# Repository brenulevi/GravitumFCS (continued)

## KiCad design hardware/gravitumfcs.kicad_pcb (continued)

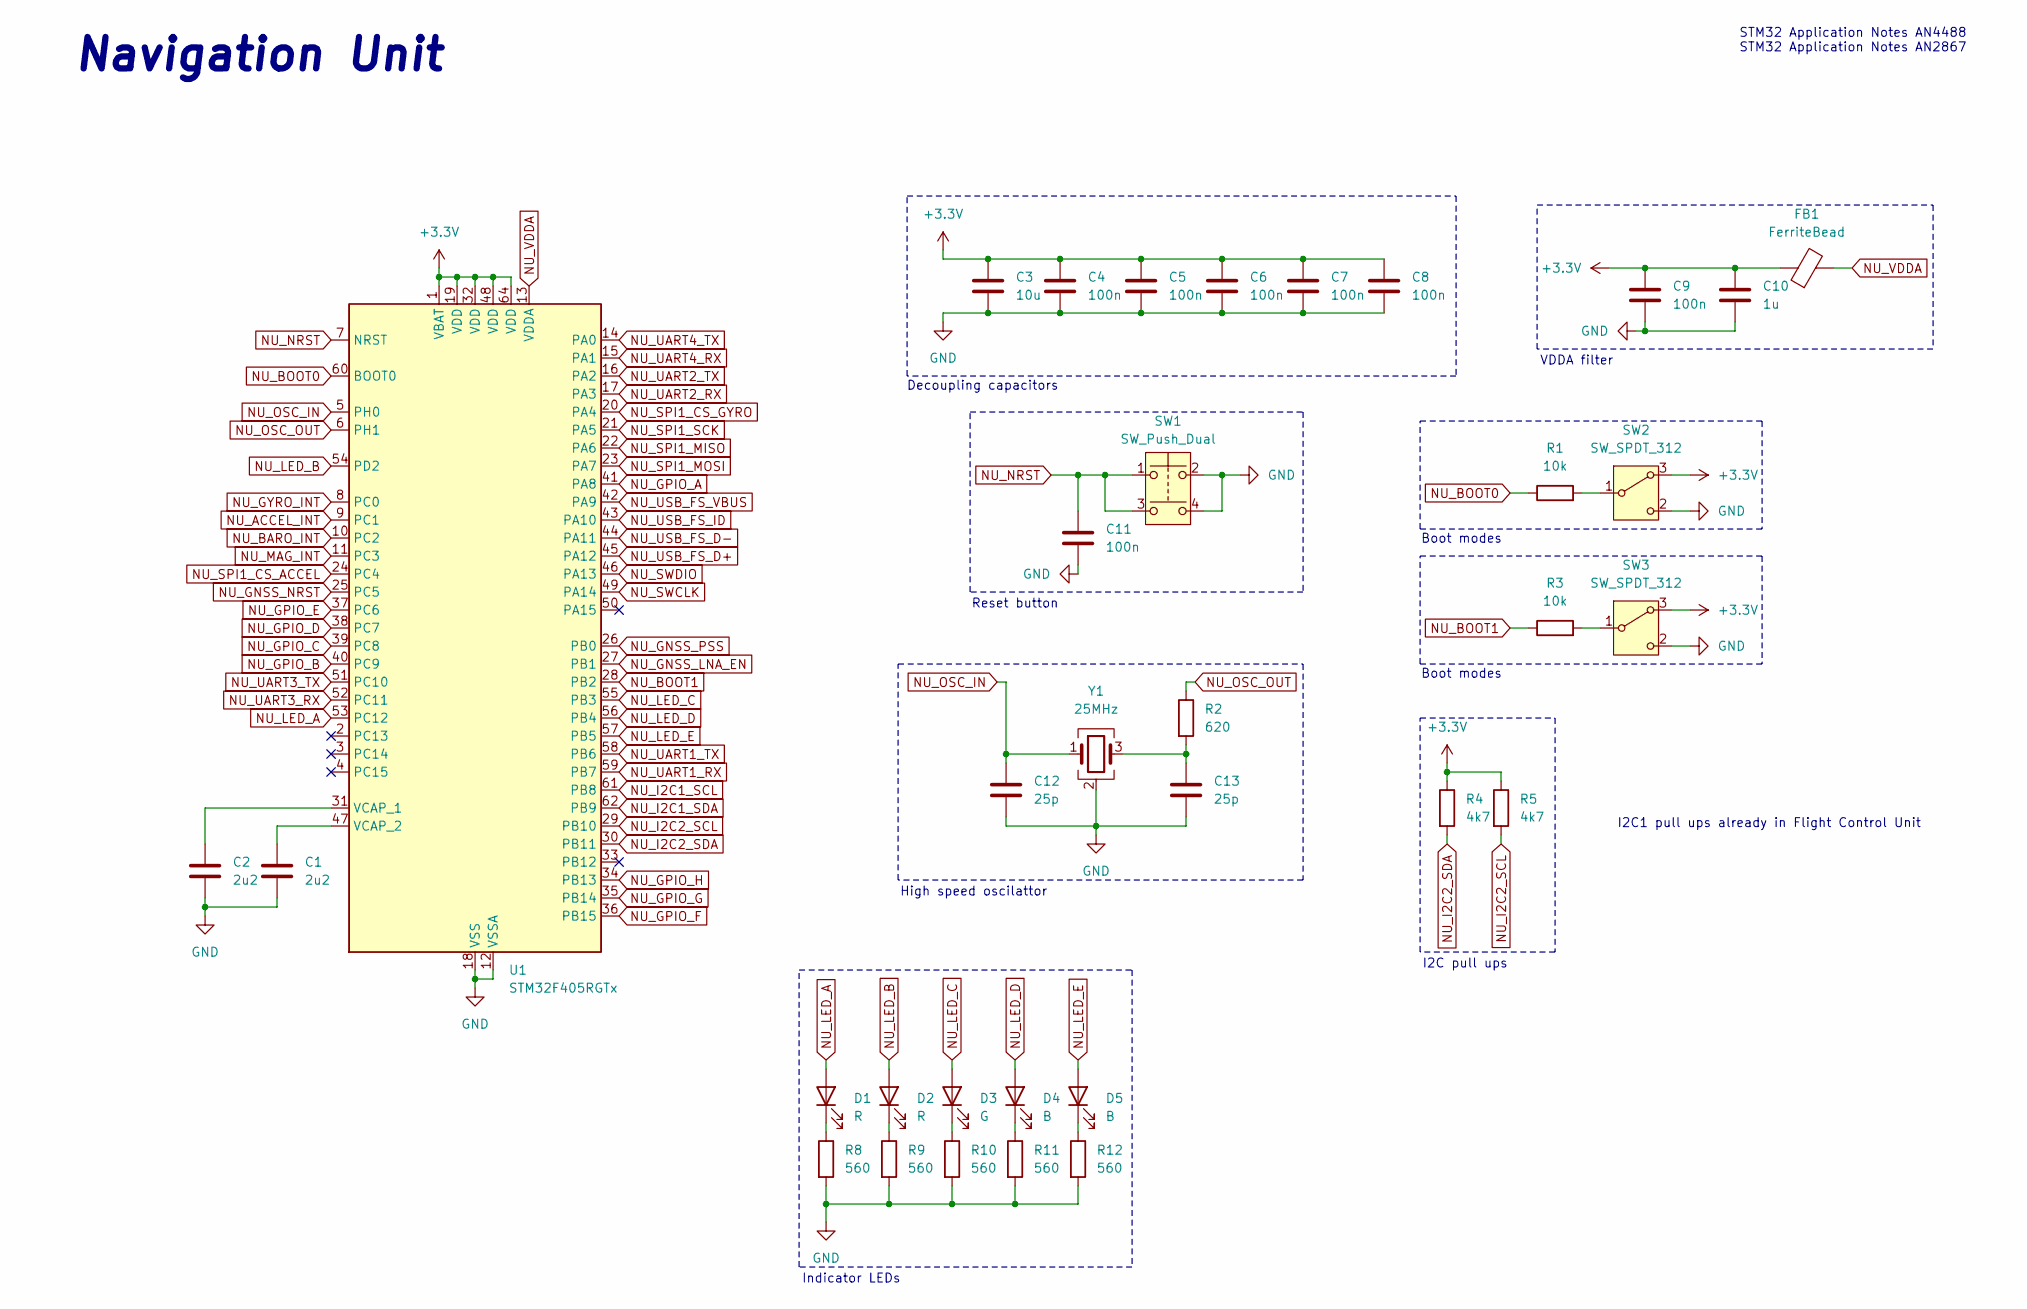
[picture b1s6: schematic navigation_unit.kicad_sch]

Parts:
C1, C2: 2u2; C_0805_2012Metric
C3: 10u; C_0603_1608Metric
C4, C5, C6, C7, C8, C9, C11: 100n; C_0402_1005Metric
C10: 1u; C_0603_1608Metric
C12, C13: 25p; C_0603_1608Metric
D1, D2: R; LED_0603_1608Metric
D3: G; LED_0603_1608Metric
D4, D5: B; LED_0603_1608Metric
FB1: FerriteBead; L_0603_1608Metric
R1, R3: 10k; R_0603_1608Metric
R2: 620; R_0603_1608Metric
R4, R5: 4k7; R_0603_1608Metric
R8, R9, R10, R11, R12: 560; R_0603_1608Metric
SW1: SW_Push_Dual; SW_TL3365AF180QG; Manufacturer Part Number TL3365AF180QG
SW2, SW3: SW_SPDT_312; SW_SPDT_PCM12; Manufacturer Part Number PCM12SMTR
U1: STM32F405RGTx; LQFP-64_10x10mm_P0.5mm; Manufacturer Part Number STM32F405RGT6
Y1: 25MHz; XTAL_ABM8G-25.000MHZ-18-D2Y-T; Manufacturer Part Number ABM8G-25.000MHZ-18-D2Y-T

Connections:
+3.3V: C3.1, C4.1, C5.1, C6.1, C7.1, C8.1, C9.1, C10.1, FB1.1, R4.1, R5.1, SW2.3 (A), SW3.3 (A), U1.1 (VBAT), U1.19 (VDD), U1.32 (VDD), U1.48 (VDD), U1.64 (VDD); also elsewhere on the board
GND: C1.2, C2.2, C3.2, C4.2, C5.2, C6.2, C7.2, C8.2, C9.2, C10.2, C11.2, C12.2, C13.2, R8.2, R9.2, R10.2, R11.2, R12.2, SW1.2, SW1.4, SW2.2 (C), SW3.2 (C), U1.12 (VSSA), U1.18 (VSS), U1.63 (VSS), Y1.2 (G), Y1.4 (G); also elsewhere on the board
NU_ACCEL_INT: U1.9 (PC1); also elsewhere on the board
NU_BARO_INT: U1.10 (PC2); also elsewhere on the board
NU_BOOT0: R1.1, U1.60 (BOOT0)
NU_BOOT1: R3.1, U1.28 (PB2)
NU_GNSS_LNA_EN: U1.27 (PB1); also elsewhere on the board
NU_GNSS_NRST: U1.25 (PC5); also elsewhere on the board
NU_GNSS_PSS: U1.26 (PB0); also elsewhere on the board
NU_GPIO_A: U1.41 (PA8); also elsewhere on the board
NU_GPIO_B: U1.40 (PC9); also elsewhere on the board
NU_GPIO_C: U1.39 (PC8); also elsewhere on the board
NU_GPIO_D: U1.38 (PC7); also elsewhere on the board
NU_GPIO_E: U1.37 (PC6); also elsewhere on the board
NU_GPIO_F: U1.36 (PB15); also elsewhere on the board
NU_GPIO_G: U1.35 (PB14); also elsewhere on the board
NU_GPIO_H: U1.34 (PB13); also elsewhere on the board
NU_GYRO_INT: U1.8 (PC0); also elsewhere on the board
NU_I2C1_SCL: U1.61 (PB8); also elsewhere on the board
NU_I2C1_SDA: U1.62 (PB9); also elsewhere on the board
NU_I2C2_SCL: R5.2, U1.29 (PB10); also elsewhere on the board
NU_I2C2_SDA: R4.2, U1.30 (PB11); also elsewhere on the board
NU_LED_A: D1.2 (A), U1.53 (PC12)
NU_LED_B: D2.2 (A), U1.54 (PD2)
NU_LED_C: D3.2 (A), U1.55 (PB3)
NU_LED_D: D4.2 (A), U1.56 (PB4)
NU_LED_E: D5.2 (A), U1.57 (PB5)
NU_MAG_INT: U1.11 (PC3); also elsewhere on the board
NU_NRST: C11.1, SW1.1, SW1.3, U1.7 (NRST); also elsewhere on the board
NU_OSC_IN: C12.1, U1.5 (PH0), Y1.1
NU_OSC_OUT: R2.1, U1.6 (PH1)
NU_SPI1_CS_ACCEL: U1.24 (PC4); also elsewhere on the board
NU_SPI1_CS_GYRO: U1.20 (PA4); also elsewhere on the board
NU_SPI1_MISO: U1.22 (PA6); also elsewhere on the board
NU_SPI1_MOSI: U1.23 (PA7); also elsewhere on the board
NU_SPI1_SCK: U1.21 (PA5); also elsewhere on the board
NU_SWCLK: U1.49 (PA14); also elsewhere on the board
NU_SWDIO: U1.46 (PA13); also elsewhere on the board
NU_UART1_RX: U1.59 (PB7); also elsewhere on the board
NU_UART1_TX: U1.58 (PB6); also elsewhere on the board
NU_UART2_RX: U1.17 (PA3); also elsewhere on the board
NU_UART2_TX: U1.16 (PA2); also elsewhere on the board
NU_UART3_RX: U1.52 (PC11); also elsewhere on the board
NU_UART3_TX: U1.51 (PC10); also elsewhere on the board
NU_UART4_RX: U1.15 (PA1); also elsewhere on the board
NU_UART4_TX: U1.14 (PA0); also elsewhere on the board
NU_USB_FS_D+: U1.45 (PA12); also elsewhere on the board
NU_USB_FS_D-: U1.44 (PA11); also elsewhere on the board
NU_USB_FS_ID: U1.43 (PA10); also elsewhere on the board
NU_USB_FS_VBUS: U1.42 (PA9); also elsewhere on the board
NU_VDDA: FB1.2, U1.13 (VDDA)
unnamed: C13.1, R2.2, Y1.3
unnamed: D1.1 (K), R8.1
unnamed: D2.1 (K), R9.1
unnamed: D3.1 (K), R10.1
unnamed: D4.1 (K), R11.1
unnamed: D5.1 (K), R12.1
unnamed: R1.2, SW2.1 (B)
unnamed: R3.2, SW3.1 (B)
unnamed: C2.1, U1.31 (VCAP_1)
unnamed: C1.1, U1.47 (VCAP_2)

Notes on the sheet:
I2C pull ups
I2C1 pull ups already in Flight Control Unit
Boot modes
Indicator LEDs
Navigation Unit
Reset button
STM32 Application Notes AN4488 STM32 Application Notes AN2867
VDDA filter
Decoupling capacitors
High speed oscilattor

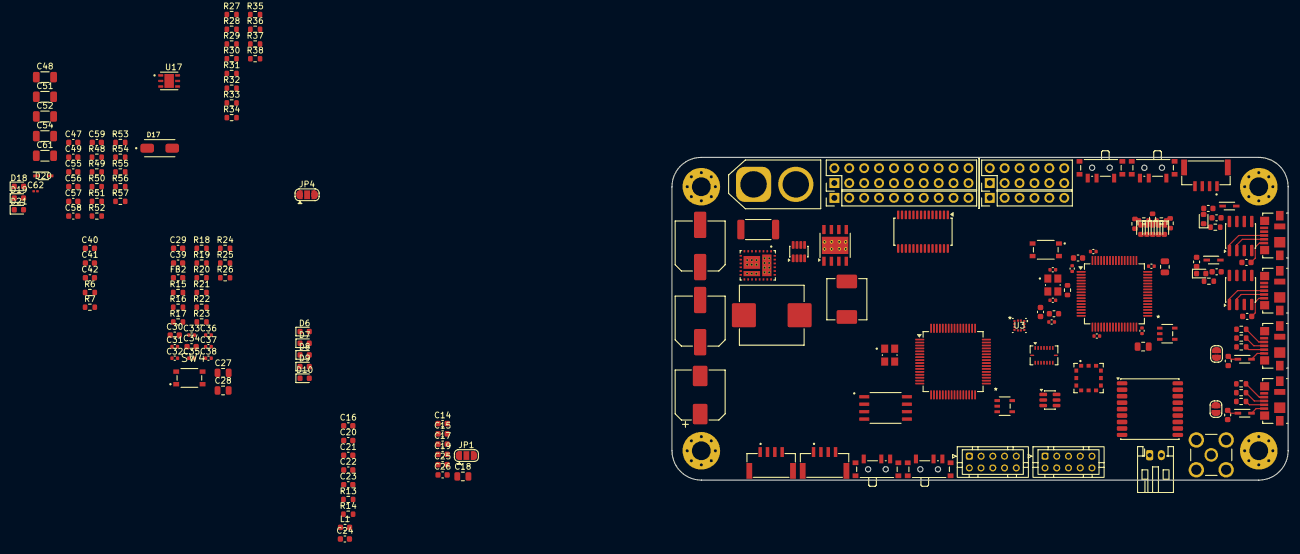
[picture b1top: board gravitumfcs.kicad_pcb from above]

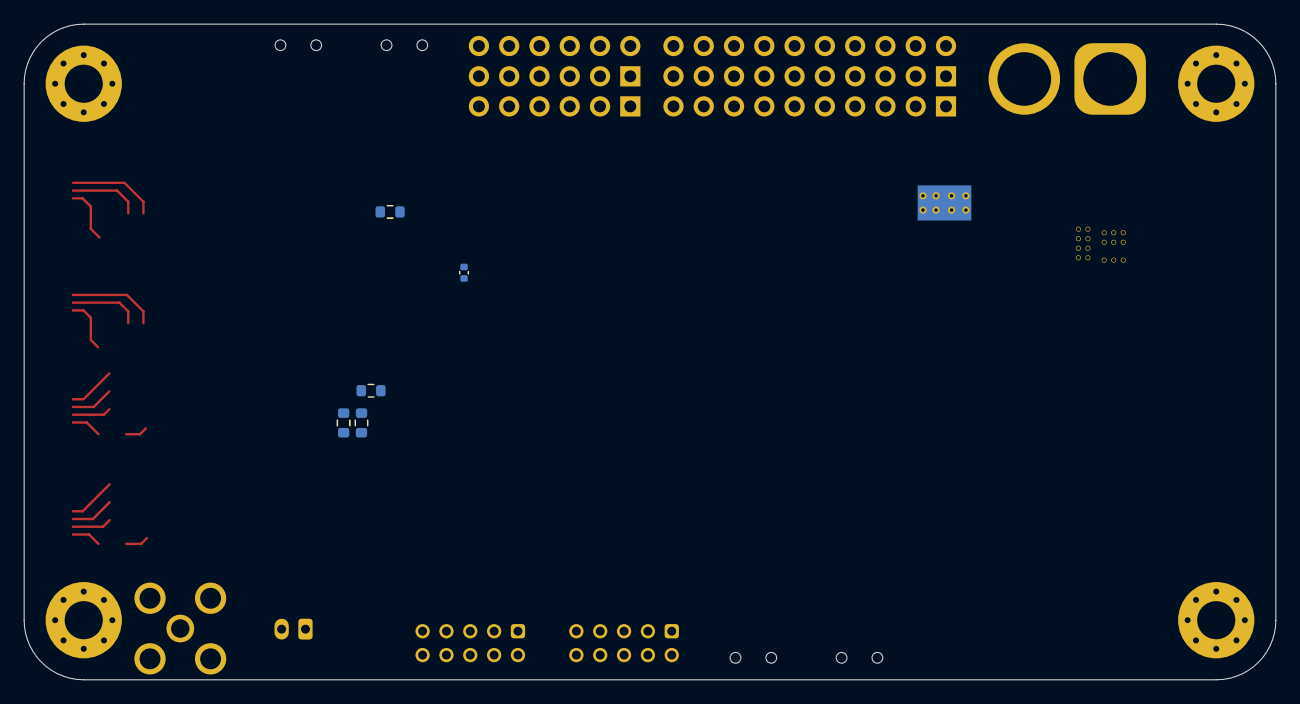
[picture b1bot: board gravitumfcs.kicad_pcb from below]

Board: 4 copper layers, 105.0 x 55.0 mm, 194 parts (5 on the bottom side), 179 nets.

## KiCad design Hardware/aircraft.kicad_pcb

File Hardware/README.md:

# FCU
- UART1: Comm with NU
- UART2: Logging Debug
- UART3: Extra UART (Radio Control)
- UART4: Extra UART (Camera)

- I2C1: Comm with NU
- I2C2: Peripherals (PWM Driver, EEPROM)

- TIM3: Actuators (CH1 Ailerons, CH2 Elevator, CH3 Rudder, CH4 Flaps)
- TIM1: Propulsions (CH2 ESC1, CH3 ESC2)

- SPI1: Peripherals (Flash)

- SWD: Coding/Debug

- SDIO: SD Card (1bit)

- GPIOA, GPIOC, GPIOE: Comm with NU (Output)
- GPIOB, GPIOD, GPIOF: Comm with NU (Input)

# NU
- UART1: Comm with FCU
- UART2: Logging Debug
- UART3: Peripheral (GNSS)
- UART4: Extra UART

- I2C1: Comm with FCU
- I2C2: Peripherals (Temperature, Baro, EEPROM, MAG)
- I2C3: Extra I2C (Pitot Sensor)

- SPI1: Peripherals (Flash) + 1 GPIO CS
- SPI2: Peripherals (IMU) + 1 GPIO CS

- SWD: Coding/Debug

- GPIO_GPS_PSS
- GPIO_GPS_LNA_EN
- GPIO_GPS_NRST

- GPIOA, GPIOC, GPIOE: Comm with NU (Input)
- GPIOB, GPIOD, GPIOF: Comm with NU (Output)

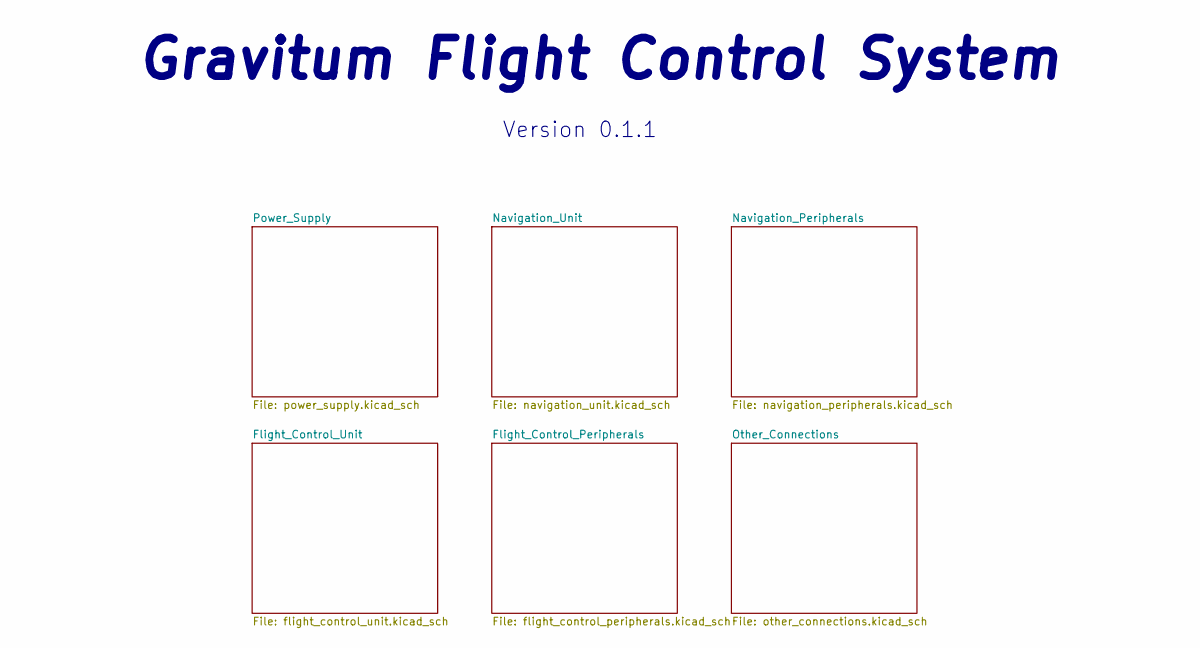
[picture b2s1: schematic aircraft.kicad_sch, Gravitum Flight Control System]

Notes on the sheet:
Gravitum Flight Control System
Version 0.1.1

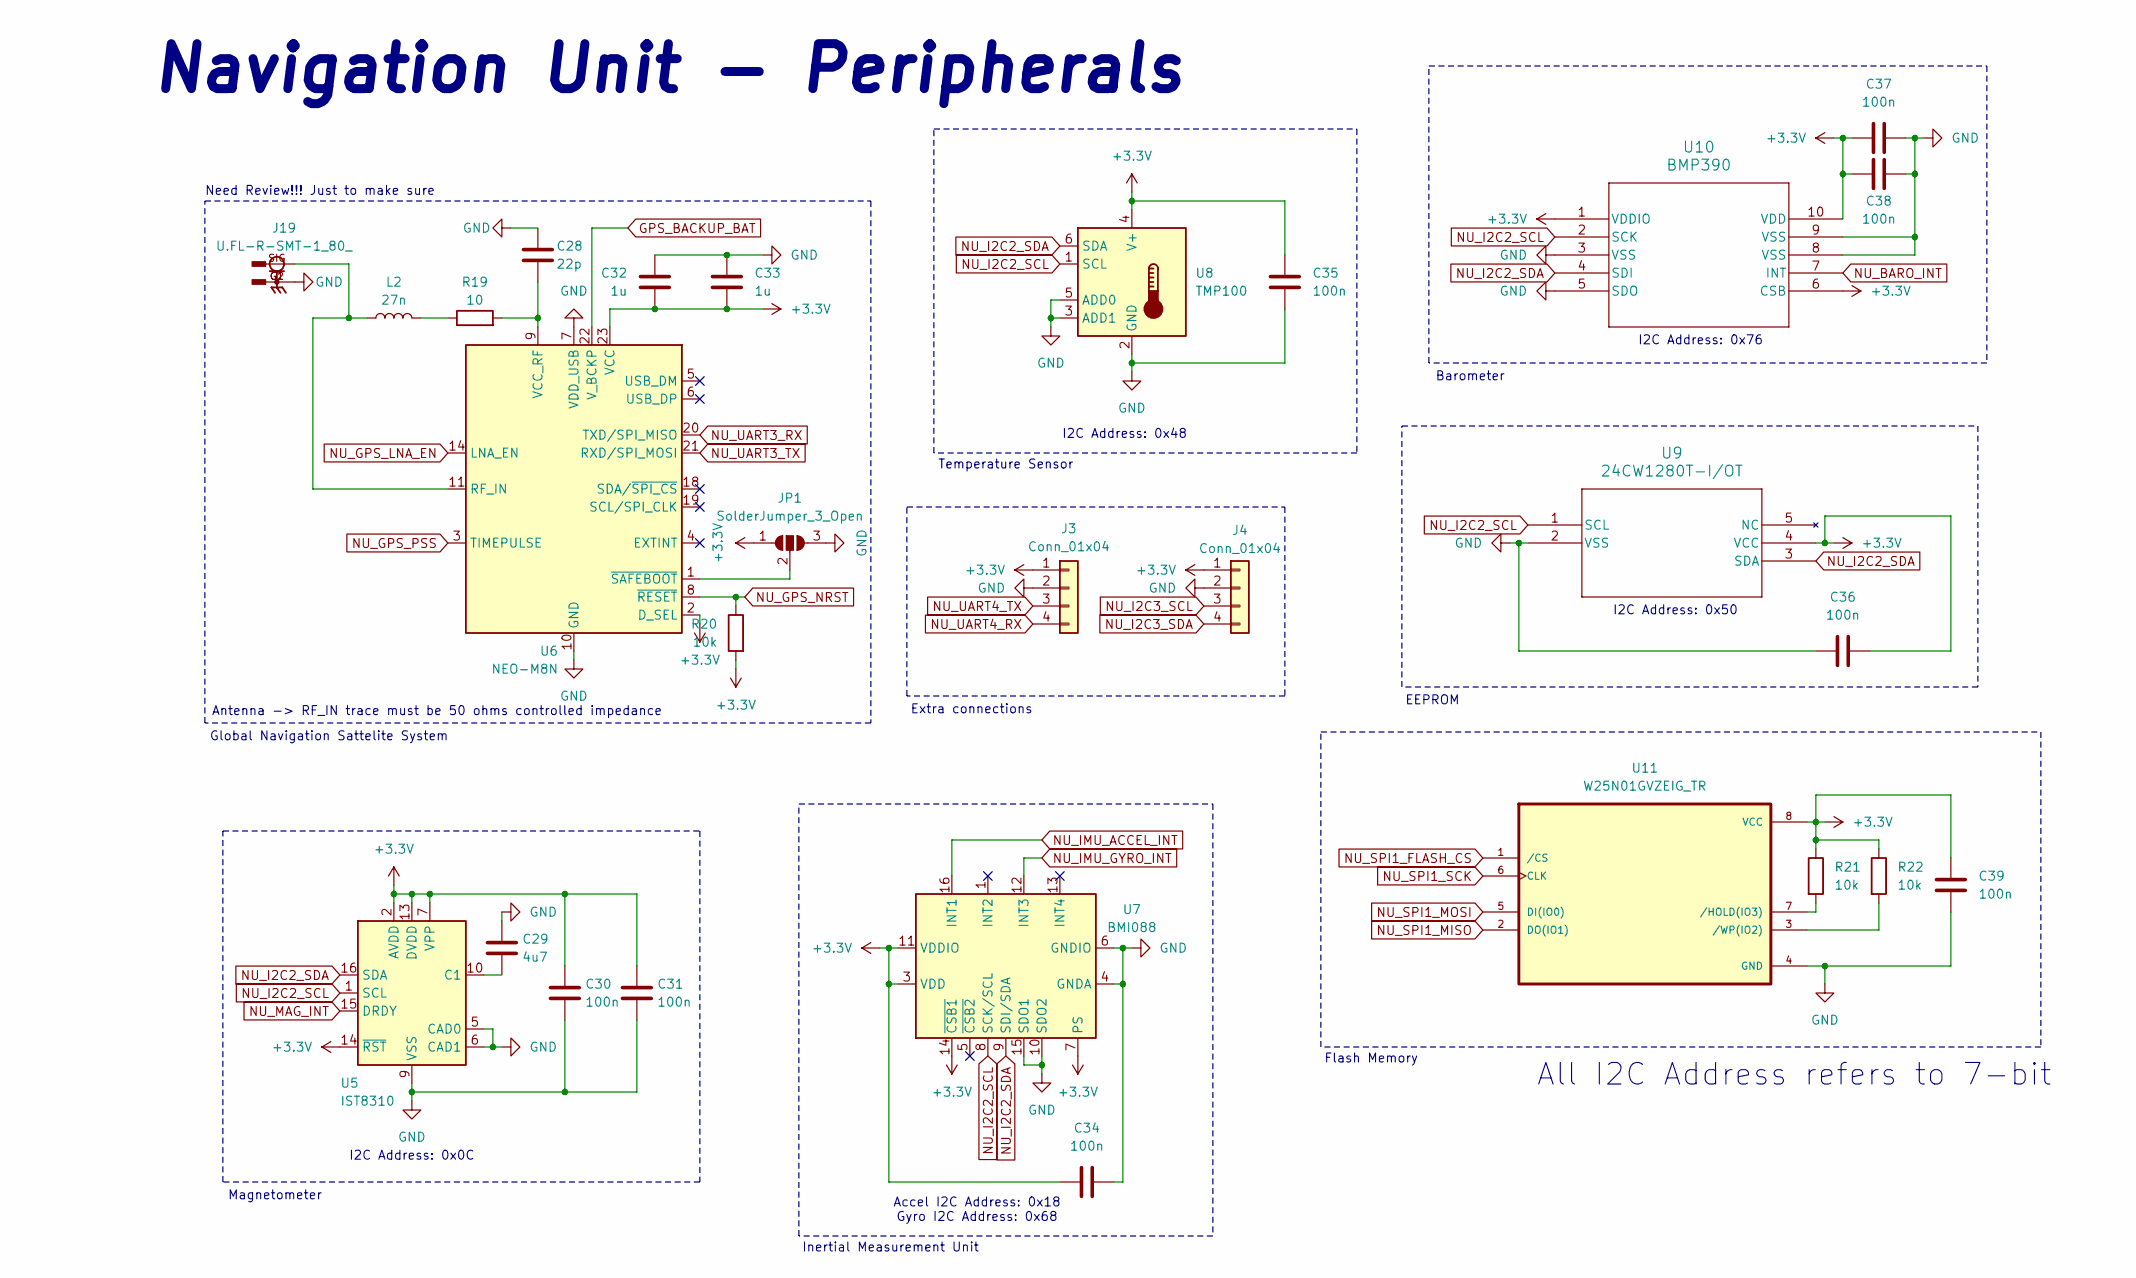
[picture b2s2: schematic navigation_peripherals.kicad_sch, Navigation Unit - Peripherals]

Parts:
C28: 22p; C_0402_1005Metric; MPN C0603C220J8GACTU
C29: 4u7; C_0402_1005Metric; MPN CL21B475KPFNNNE
C30, C31, C34, C35, C36, C37, C38, C39: 100n; C_0402_1005Metric; MPN C0603C104K8RACTU
C32, C33: 1u; C_0402_1005Metric; MPN CL10B105KP8NNNC
J3, J4: Conn_01x04; JST_PH_S4B-PH-K_1x04_P2.00mm_Horizontal; MPN S4B-PH-K-S
J19: U.FL-R-SMT-1_80_; HIROSE_U.FL-R-SMT-1_80_; PARTREV Jul.1.2022
JP1: SolderJumper_3_Open; SolderJumper-3_P1.3mm_Open_RoundedPad1.0x1.5mm_NumberLabels
L2: 27n; L_0402_1005Metric; MPN B82496C3270J000
R19: 10; R_0402_1005Metric; MPN RMCF0603FT10R0
R20, R21, R22: 10k; R_0402_1005Metric; MPN RC0603FR-0710KL
U5: IST8310; LGA-16_3x3mm_P0.5mm; MPN IST8310
U6: NEO-M8N; XCVR_NEO-M8N-0; MPN NEO-M8N-0
U7: BMI088; Bosch_LGA-16_4.5x3mm_P0.5mm_LayoutBorder7x1y_ClockwisePinNu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; MPN BMI088
U8: TMP100; SOT-23-6; MPN TMP100NA-3K
U9: 24CW1280T-I/OT; SOT-23-5_2P9X1P6_MCH; MPN 24CW1280T-I/OT
U10: BMP390; 10LGA_2X2X0p75_BOS; MPN BMP390
U11: W25N01GVZEIG_TR; SON127P800X600X80-9N; MPN W25N01GVZEIG-TR

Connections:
+3.3V: C30.1, C31.1, C32.2, C33.2, C34.1, C35.2, C36.1, C37.2, C38.2, C39.1, J3.1, J4.1, JP1.1 (A), R20.2, R21.1, R22.1, U5.2 (AVDD), U5.7 (VPP), U5.13 (DVDD), U5.14 (~RST), U6.2 (D_SEL), U6.23 (VCC), U7.3 (VDD), U7.7 (PS), U7.11 (VDDIO), U7.14 (~CSB1), U8.4 (V+), U9.4 (VCC), U10.1 (VDDIO), U10.6 (CSB), U10.10 (VDD), U11.8 (VCC); also elsewhere on the board
GND: C28.1, C29.1, C30.2, C31.2, C32.1, C33.1, C34.2, C35.1, C36.2, C37.1, C38.1, C39.2, J3.2, J4.2, J19.G1, J19.G2, JP1.3 (B), U5.5 (CAD0), U5.6 (CAD1), U5.9 (VSS), U5.11 (VSS), U6.7 (VDD_USB), U6.10 (GND), U6.12 (GND), U6.13 (GND), U6.24 (GND), U7.2 (GNDA), U7.4 (GNDA), U7.6 (GNDIO), U7.10 (SDO2), U7.15 (SDO1), U8.2 (GND), U8.3 (ADD1), U8.5 (ADD0), U9.2 (VSS), U10.3 (VSS), U10.5 (SDO), U10.8 (VSS), U10.9 (VSS), U11.4 (GND); also elsewhere on the board
GPS_BACKUP_BAT: U6.22 (V_BCKP); also elsewhere on the board
NU_BARO_INT: U10.7 (INT); also elsewhere on the board
NU_GPS_LNA_EN: U6.14 (LNA_EN); also elsewhere on the board
NU_GPS_NRST: R20.1, U6.8 (~RESET); also elsewhere on the board
NU_GPS_PSS: U6.3 (TIMEPULSE); also elsewhere on the board
NU_I2C2_SCL: U5.1 (SCL), U7.8 (SCK/SCL), U8.1 (SCL), U9.1 (SCL), U10.2 (SCK); also elsewhere on the board
NU_I2C2_SDA: U5.16 (SDA), U7.9 (SDI/SDA), U8.6 (SDA), U9.3 (SDA), U10.4 (SDI); also elsewhere on the board
NU_I2C3_SCL: J4.3; also elsewhere on the board
NU_I2C3_SDA: J4.4; also elsewhere on the board
NU_IMU_ACCEL_INT: U7.16 (INT1); also elsewhere on the board
NU_IMU_GYRO_INT: U7.12 (INT3); also elsewhere on the board
NU_MAG_INT: U5.15 (DRDY); also elsewhere on the board
NU_SPI1_FLASH_CS: U11.1 (/CS); also elsewhere on the board
NU_SPI1_MISO: U11.2 (DO(IO1)); also elsewhere on the board
NU_SPI1_MOSI: U11.5 (DI(IO0)); also elsewhere on the board
NU_SPI1_SCK: U11.6 (CLK); also elsewhere on the board
NU_UART3_RX: U6.20 (TXD/SPI_MISO); also elsewhere on the board
NU_UART3_TX: U6.21 (RXD/SPI_MOSI); also elsewhere on the board
NU_UART4_RX: J3.4; also elsewhere on the board
NU_UART4_TX: J3.3; also elsewhere on the board
unnamed: JP1.2 (C), U6.1 (~SAFEBOOT)
unnamed: L2.2, R19.1
unnamed: C29.2, U5.10 (C1)
unnamed: J19.SIG, L2.1, U6.11 (RF_IN)
unnamed: C28.2, R19.2, U6.9 (VCC_RF)
unnamed: R21.2, U11.7 (/HOLD(IO3))
unnamed: R22.2, U11.3 (/WP(IO2))

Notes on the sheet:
Magnetometer
Navigation Unit - Peripherals
I2C Address: 0x48
Flash Memory
I2C Address: 0x76
Barometer
Temperature Sensor
Accel I2C Address: 0x18 Gyro I2C Address: 0x68
EEPROM
Need Review!!! Just to make sure
Global Navigation Sattelite System
Inertial Measurement Unit
All I2C Address refers to 7-bit
Antenna -> RF_IN trace must be 50 ohms controlled impedance
I2C Address: 0x0C
I2C Address: 0x50
Extra connections

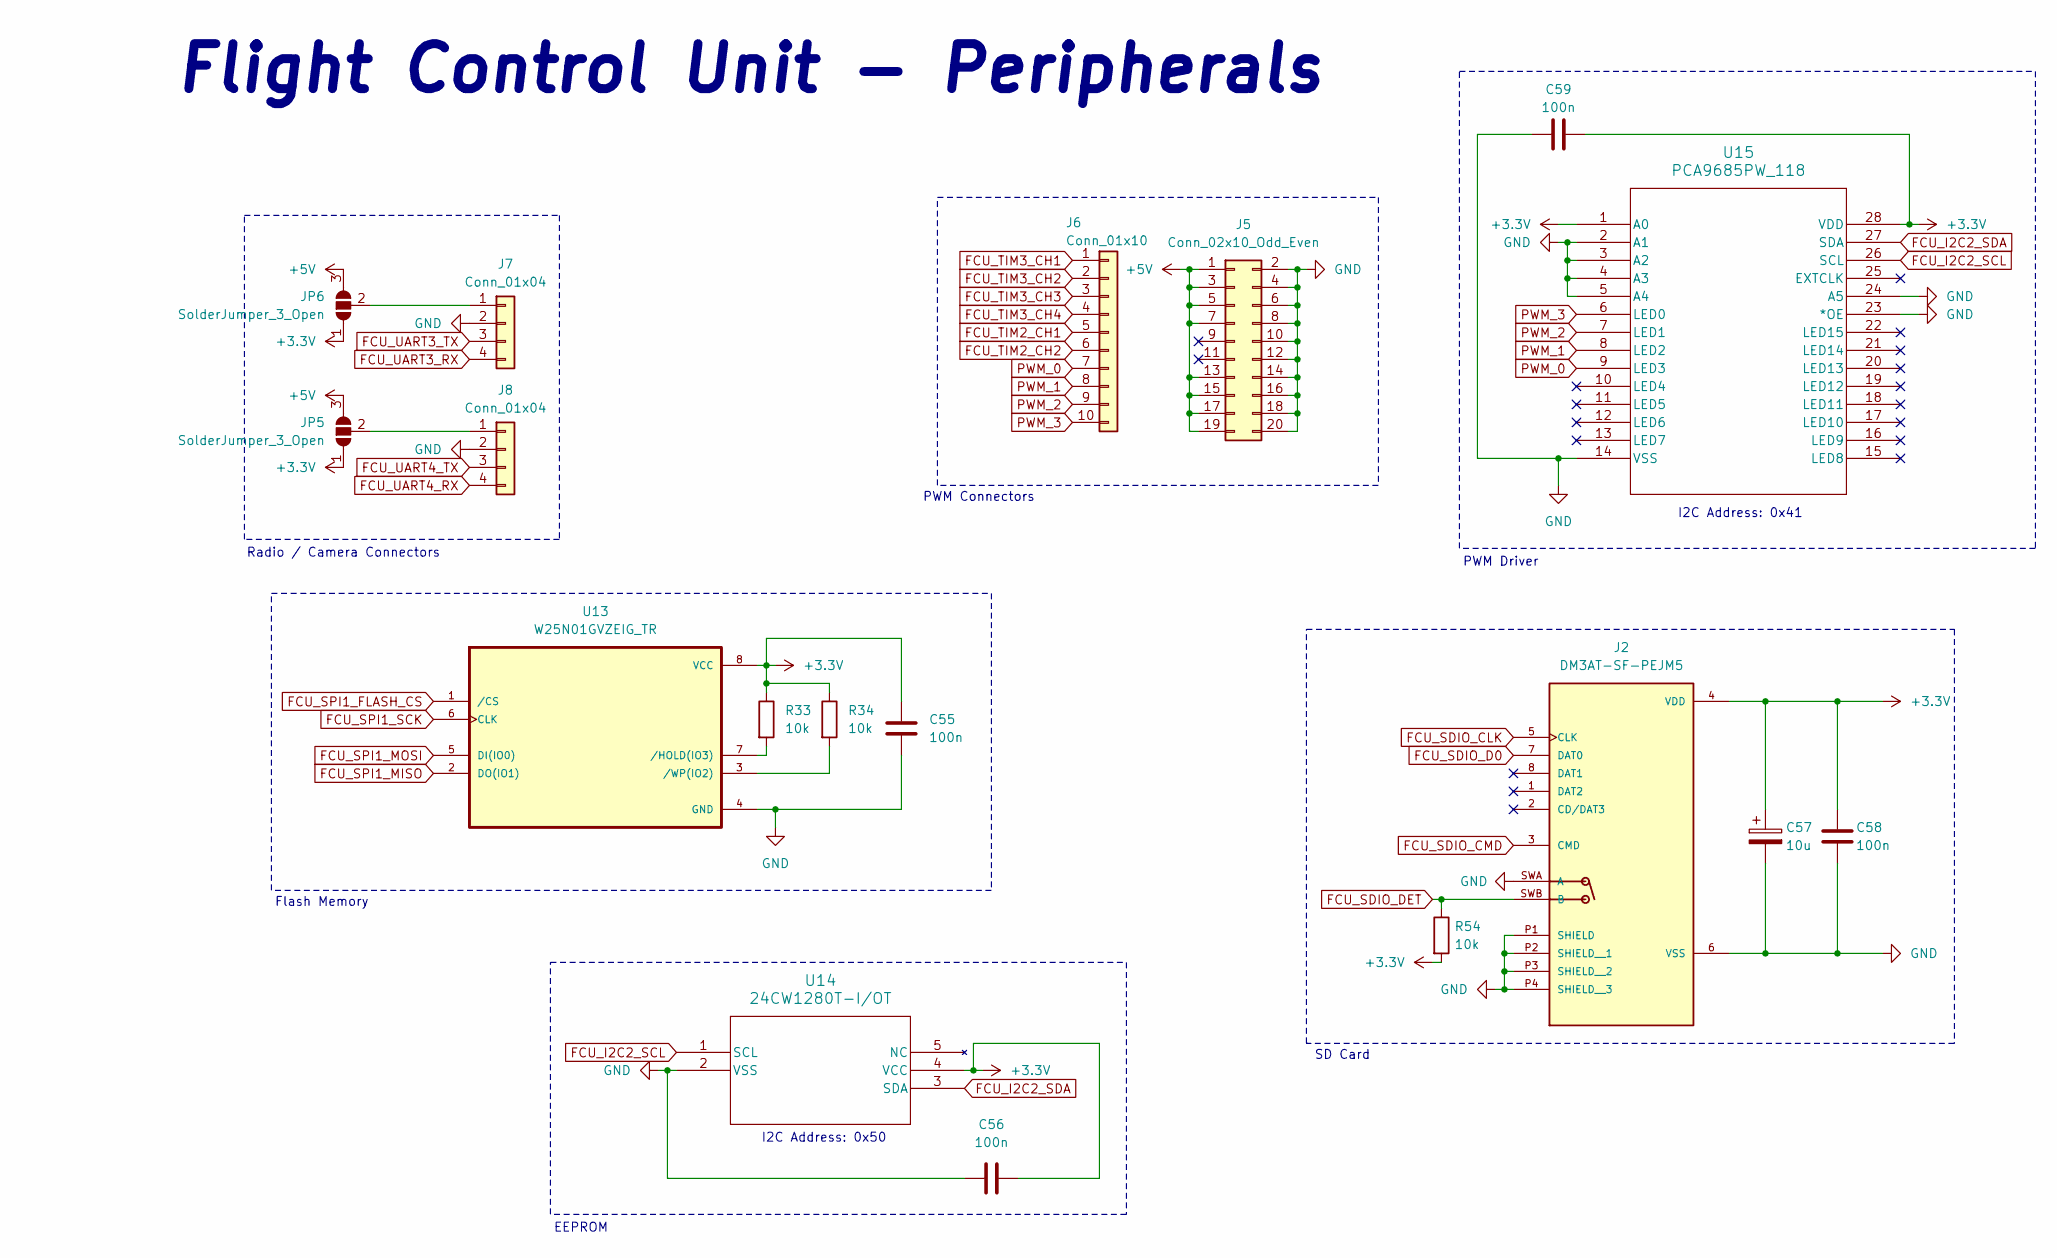
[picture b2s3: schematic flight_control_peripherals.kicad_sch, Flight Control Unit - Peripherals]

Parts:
C55, C56, C58, C59: 100n; C_0402_1005Metric; MPN C0603C104K8RACTU
C57: 10u; C_0603_1608Metric; MPN TAJA106K010TNJ
J2: DM3AT-SF-PEJM5; HRS_DM3AT-SF-PEJM5; PARTREV 20200913
J5: Conn_02x10_Odd_Even; PinHeader_2x10_P2.54mm_Vertical
J6: Conn_01x10; PinHeader_1x10_P2.54mm_Vertical
J7, J8: Conn_01x04; JST_PH_S4B-PH-K_1x04_P2.00mm_Horizontal; MPN S4B-PH-K-S
JP5, JP6: SolderJumper_3_Open; SolderJumper-3_P1.3mm_Open_RoundedPad1.0x1.5mm_NumberLabels
R33, R34, R54: 10k; R_0402_1005Metric; MPN RC0603FR-0710KL
U13: W25N01GVZEIG_TR; SON127P800X600X80-9N; MPN W25N01GVZEIG-TR
U14: 24CW1280T-I/OT; SOT-23-5_2P9X1P6_MCH; MPN 24CW1280T-I/OT
U15: PCA9685PW_118; TSSOP28_SOT361-1_NXP; MPN PCA9685PW,118

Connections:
+3.3V: C55.1, C56.1, C57.1, C58.1, C59.1, J2.4 (VDD), JP5.1 (A), JP6.1 (A), R33.1, R34.1, R54.2, U13.8 (VCC), U14.4 (VCC), U15.1 (A0), U15.28 (VDD); also elsewhere on the board
+5V: J5.1, J5.3, J5.5, J5.7, J5.13, J5.15, J5.17, J5.19, JP5.3 (B), JP6.3 (B); also elsewhere on the board
FCU_I2C2_SCL: U14.1 (SCL), U15.26 (SCL); also elsewhere on the board
FCU_I2C2_SDA: U14.3 (SDA), U15.27 (SDA); also elsewhere on the board
FCU_SDIO_CLK: J2.5 (CLK); also elsewhere on the board
FCU_SDIO_CMD: J2.3 (CMD); also elsewhere on the board
FCU_SDIO_D0: J2.7 (DAT0); also elsewhere on the board
FCU_SDIO_DET: J2.SWB (B), R54.1; also elsewhere on the board
FCU_SPI1_FLASH_CS: U13.1 (/CS); also elsewhere on the board
FCU_SPI1_MISO: U13.2 (DO(IO1)); also elsewhere on the board
FCU_SPI1_MOSI: U13.5 (DI(IO0)); also elsewhere on the board
FCU_SPI1_SCK: U13.6 (CLK); also elsewhere on the board
FCU_TIM2_CH1: J6.5; also elsewhere on the board
FCU_TIM2_CH2: J6.6; also elsewhere on the board
FCU_TIM3_CH1: J6.1; also elsewhere on the board
FCU_TIM3_CH2: J6.2; also elsewhere on the board
FCU_TIM3_CH3: J6.3; also elsewhere on the board
FCU_TIM3_CH4: J6.4; also elsewhere on the board
FCU_UART3_RX: J7.4; also elsewhere on the board
FCU_UART3_TX: J7.3; also elsewhere on the board
FCU_UART4_RX: J8.4; also elsewhere on the board
FCU_UART4_TX: J8.3; also elsewhere on the board
GND: C55.2, C56.2, C57.2, C58.2, C59.2, J2.6 (VSS), J2.P1 (SHIELD), J2.P2 (SHIELD__1), J2.P3 (SHIELD__2), J2.P4 (SHIELD__3), J2.SWA (A), J5.2, J5.4, J5.6, J5.8, J5.10, J5.12, J5.14, J5.16, J5.18, J5.20, J7.2, J8.2, U13.4 (GND), U14.2 (VSS), U15.2 (A1), U15.3 (A2), U15.4 (A3), U15.5 (A4), U15.14 (VSS), U15.23 (*OE), U15.24 (A5); also elsewhere on the board
unnamed: J7.1, JP6.2 (C)
unnamed: J8.1, JP5.2 (C)
unnamed: R33.2, U13.7 (/HOLD(IO3))
unnamed: R34.2, U13.3 (/WP(IO2))
PWM_0: J6.7, U15.9 (LED3)
PWM_1: J6.8, U15.8 (LED2)
PWM_2: J6.9, U15.7 (LED1)
PWM_3: J6.10, U15.6 (LED0)

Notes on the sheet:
I2C Address: 0x50
I2C Address: 0x41
Radio / Camera Connectors
SD Card
PWM Driver
PWM Connectors
Flash Memory
Flight Control Unit - Peripherals
EEPROM

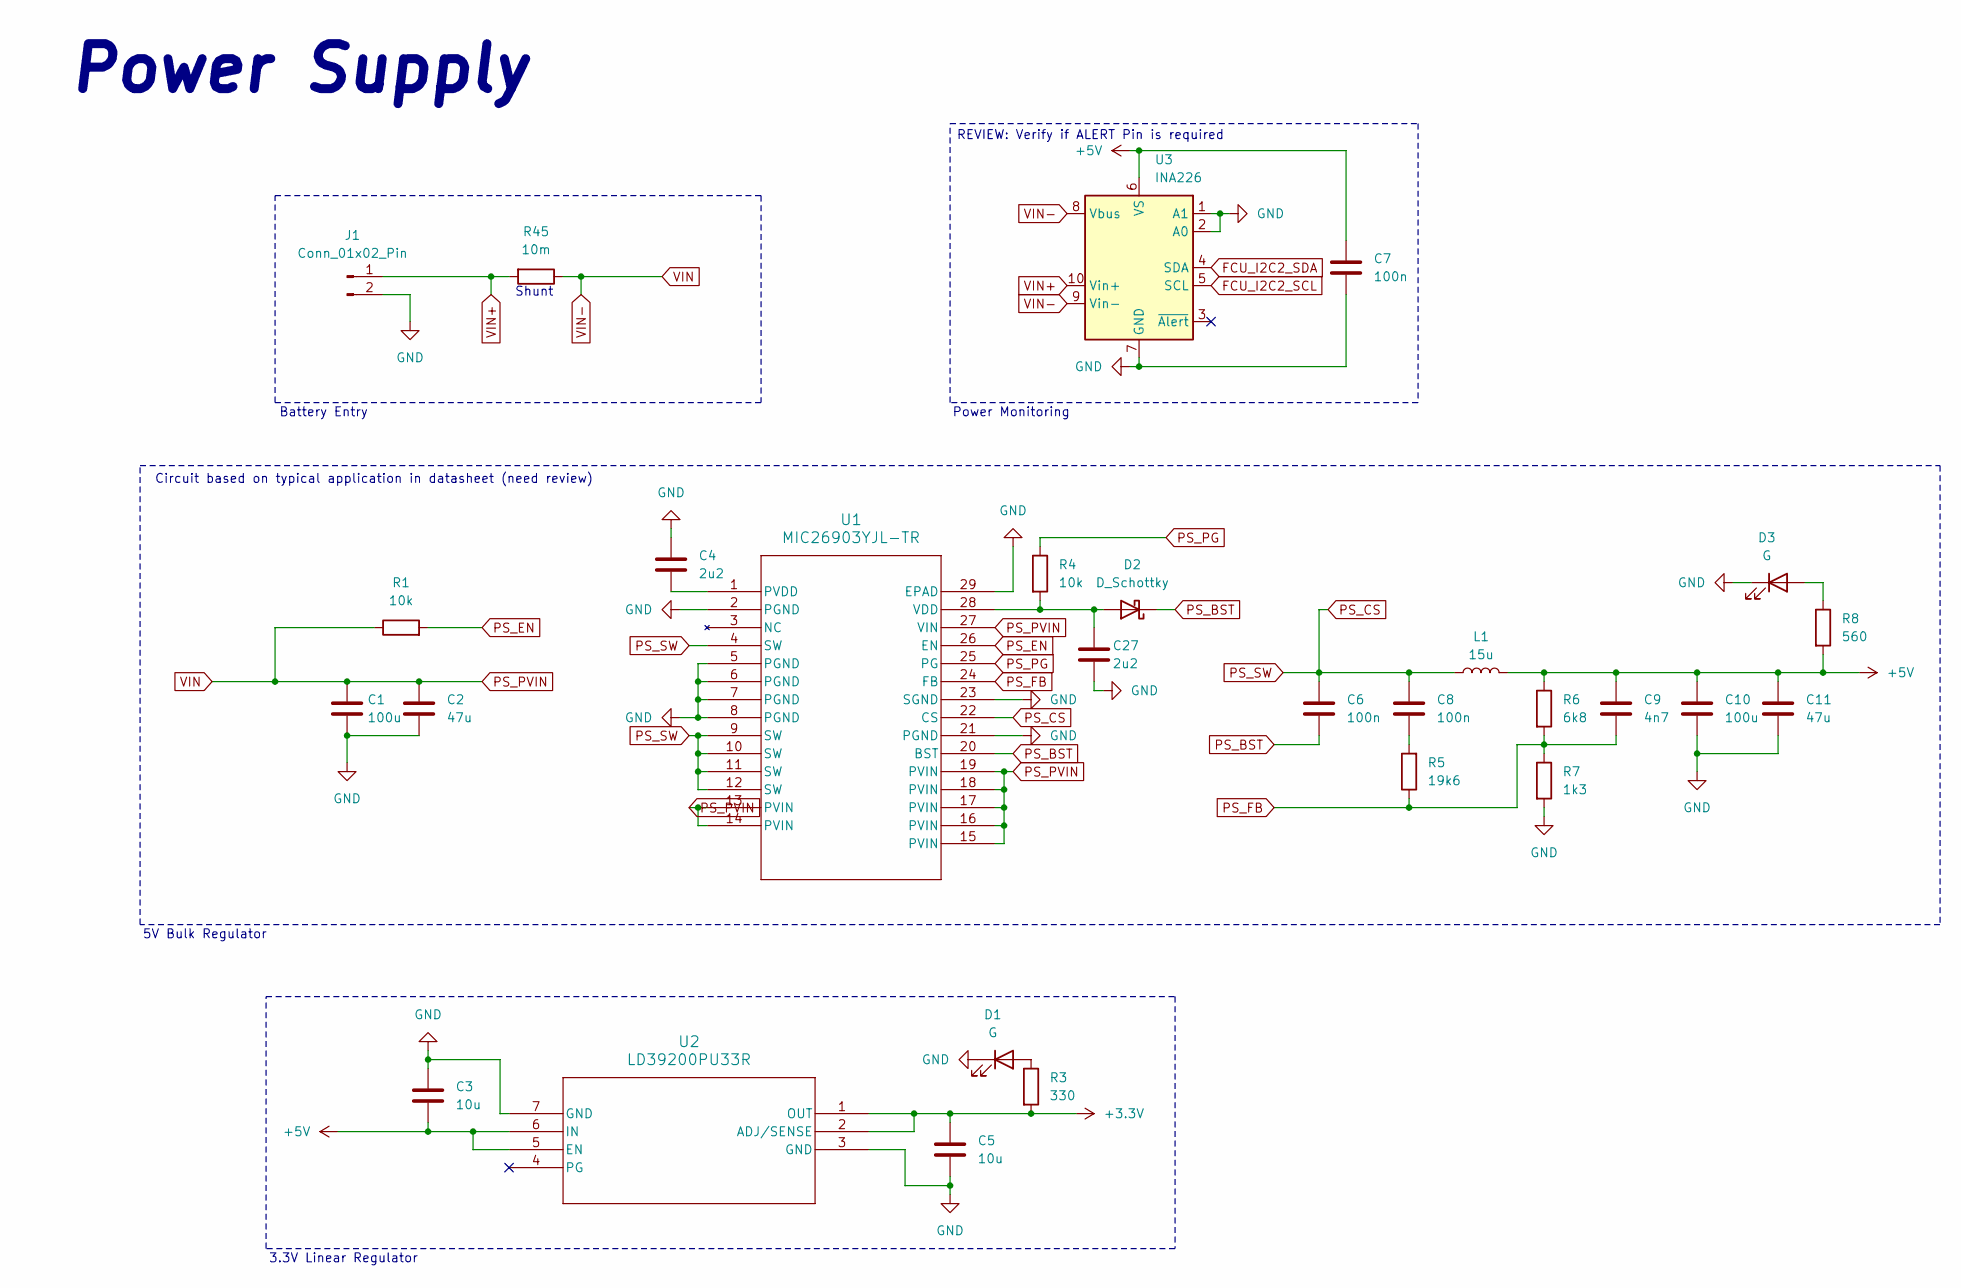
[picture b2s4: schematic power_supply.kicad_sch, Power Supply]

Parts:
C1, C10: 100u; C_Elec_6.3x7.7; MPN A768EB107M1ELAS036
C2, C11: 47u; C_1206_3216Metric; MPN C3216X5R1E476M160AC
C3, C5: 10u; C_0603_1608Metric; MPN CL21B106KPQNNNE
C4, C27: 2u2; C_0603_1608Metric; MPN 08053C225KAT2A
C6, C8: 100n; C_0603_1608Metric; MPN C0603C104K3RACTU
C7: 100n; C_0402_1005Metric; MPN C0603C104K3RACTU
C9: 4n7; C_0603_1608Metric; MPN C0603C472F3GACTU
D1, D3: G; LED_0402_1005Metric; MPN LTST-S270KGKT
D2: D_Schottky; D_SOD-323_HandSoldering; MPN SD103AWS
J1: Conn_01x02_Pin; AMASS_XT60-M_1x02_P7.20mm_Vertical; MPN 11864
L1: 15u; IND_SRP1038A_BRN; MPN PA4343-103ANLT
R1: 10k; R_0603_1608Metric_Pad0.98x0.95mm_HandSolder; MPN RC0603FR-0710KL
R3: 330; R_0402_1005Metric; MPN RC0603JR-07330RL
R4: 10k; R_0402_1005Metric; MPN RC0603FR-0710KL
R5: 19k6; R_0603_1608Metric_Pad0.98x0.95mm_HandSolder; MPN CRCW060319K6FKEAC
R6: 6k8; R_0603_1608Metric_Pad0.98x0.95mm_HandSolder; MPN RC0603JR-076K8L
R7: 1k3; R_0603_1608Metric_Pad0.98x0.95mm_HandSolder; MPN RC0603JR-071K3L
R8: 560; R_0402_1005Metric; MPN RMCF0603FT560R
R45: 10m; R_2512_6332Metric_Pad1.40x3.35mm_HandSolder; MPN CRF2512-FZ-R010ELF
U1: MIC26903YJL-TR; MLF28_5X6_MCH; MPN MIC26903YJL-TR
U2: LD39200PU33R; SON_DFN6_3X3_STM; MPN LD39200PU33R
U3: INA226; DGS10; MPN INA226AIDGST

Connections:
+3.3V: C5.1, R3.2, U2.1 (OUT), U2.2 (ADJ/SENSE); also elsewhere on the board
+5V: C3.2, C7.1, C9.1, C10.1, C11.1, L1.2, R6.1, R8.2, U2.5 (EN), U2.6 (IN), U3.6 (VS); also elsewhere on the board
FCU_I2C2_SCL: U3.5 (SCL); also elsewhere on the board
FCU_I2C2_SDA: U3.4 (SDA); also elsewhere on the board
GND: C1.2, C2.2, C3.1, C4.1, C5.2, C7.2, C10.2, C11.2, C27.2, D1.1 (K), D3.1 (K), J1.2, R7.2, U1.2 (PGND), U1.5 (PGND), U1.6 (PGND), U1.7 (PGND), U1.8 (PGND), U1.21 (PGND), U1.23 (SGND), U1.29 (EPAD), U2.3 (GND), U2.7 (GND), U3.1 (A1), U3.2 (A0), U3.7 (GND); also elsewhere on the board
unnamed: C8.2, R5.2
unnamed: D1.2 (A), R3.1
unnamed: C27.1, D2.2 (A), R4.2, U1.28 (VDD)
unnamed: D3.2 (A), R8.1
unnamed: C4.2, U1.1 (PVDD)
PS_BST: C6.2, D2.1 (K), U1.20 (BST)
PS_CS: C6.1, C8.1, L1.1, U1.4 (SW), U1.9 (SW), U1.10 (SW), U1.11 (SW), U1.12 (SW), U1.22 (CS)
PS_EN: R1.2, U1.26 (EN)
PS_FB: C9.2, R5.1, R6.2, R7.1, U1.24 (FB)
PS_PG: R4.1, U1.25 (PG)
PS_PVIN: C1.1, C2.1, R1.1, R45.1, U1.13 (PVIN), U1.14 (PVIN), U1.15 (PVIN), U1.16 (PVIN), U1.17 (PVIN), U1.18 (PVIN), U1.19 (PVIN), U1.27 (VIN), U3.8 (Vbus), U3.9 (Vin-)
VIN+: J1.1, R45.2, U3.10 (Vin+)

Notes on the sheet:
Power Supply
5V Bulk Regulator
REVIEW: Verify if ALERT Pin is required
Circuit based on typical application in datasheet (need review)
Battery Entry
3.3V Linear Regulator
Shunt
Power Monitoring
